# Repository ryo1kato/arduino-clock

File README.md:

## Arduino Blink "minute repeater" Clock (ATtiny85 version)

A clock with blinking LED indicating the time of day. &nbsp;
LED version of a [repeater](https://en.wikipedia.org/wiki/Repeater_%28horology%29)
You can tell a time in the dark, from distance, w/o glasses. &nbsp;
Useful if you're myopic and don't have glasses or smartphone within reach of your hand when you're in the bed (like me, with my two kids blocking my both sides). &nbsp;
LED brightness is automatically adjusted with light sensor (CdS photo cell)
The design uses AVR ATtiny85 micro controller and DS3231 RTC chip with "smart" RGB LED WS2812B.

## Telling Time
* Blinking in white: base hour of 0, 3, 6, or 9 o'clock.
    - once        : 0 o'clock
    - twice       : 3 o'clock
    - three times : 6 o'clock
    - four times  : 9 o'clock

* Blinking in <span style='color: #00AA00'>**green**</span>: add one or two hours to the above base hour.
    - example: blinking in white for three times, and then twice in green indicates 8 o'clock (8am or 8pm)

* Blinking in <span style='color: red'>**red**</span>: 10 minutes per blink.
    - example: blinking in red for four times: 40 minutes

* Blinking in <span style='color: blue'>**blue**</span>(fast): one minute per blink.

The clock blinks in white -> green -> blue -> blue, skipping some of the colors, for example, skipping red if the time is 10:02 (in which case it blinks in whilte three times, in green once, skips green, and in blue twice)

After completing this cycle, clock sleeps about 3 seconds and start a new cycle.

### Adjusting Time
Long press *Hour* and/or *Minute* button until they start blinking slowly in max brightness.

* Long press *Hour* button : advance time by 60 minutes (blinks in green)
* Long press *Minute* button : advance time by one minutes (blinks in blue)
* Long press **both** buttons : advance time by ten minutes (blinks in red)

You need to keep the buttons pressed and wait for an time indicating cycle to complete, until it starts blinking slowly and brightly.

### Build of Materials
* PCB
    - SMD (rev 0.5.1) [OSH Park](https://oshpark.com/shared_projects/CKZP3omf)
    - THT (rev 0.2) [OSH Park](https://oshpark.com/shared_projects/mC1U04Ox)
* BOM: [bom.txt](schematic/bom.txt)

### Port Assignment
* RST (GPIO #5) - Hour & Minute Buttons (using ADC above 2.2v reset threshold)
* GPIO #0       -  I2C SDA to RTC
* GPIO #1       -  Smart LED NeoPixel WS2812B
* GPIO #2       -  I2C SCL to RTC
* GPIO #3       -  Photo Cell
* GPIO #4       -  Power Control for LED, RTC, Photo Cell

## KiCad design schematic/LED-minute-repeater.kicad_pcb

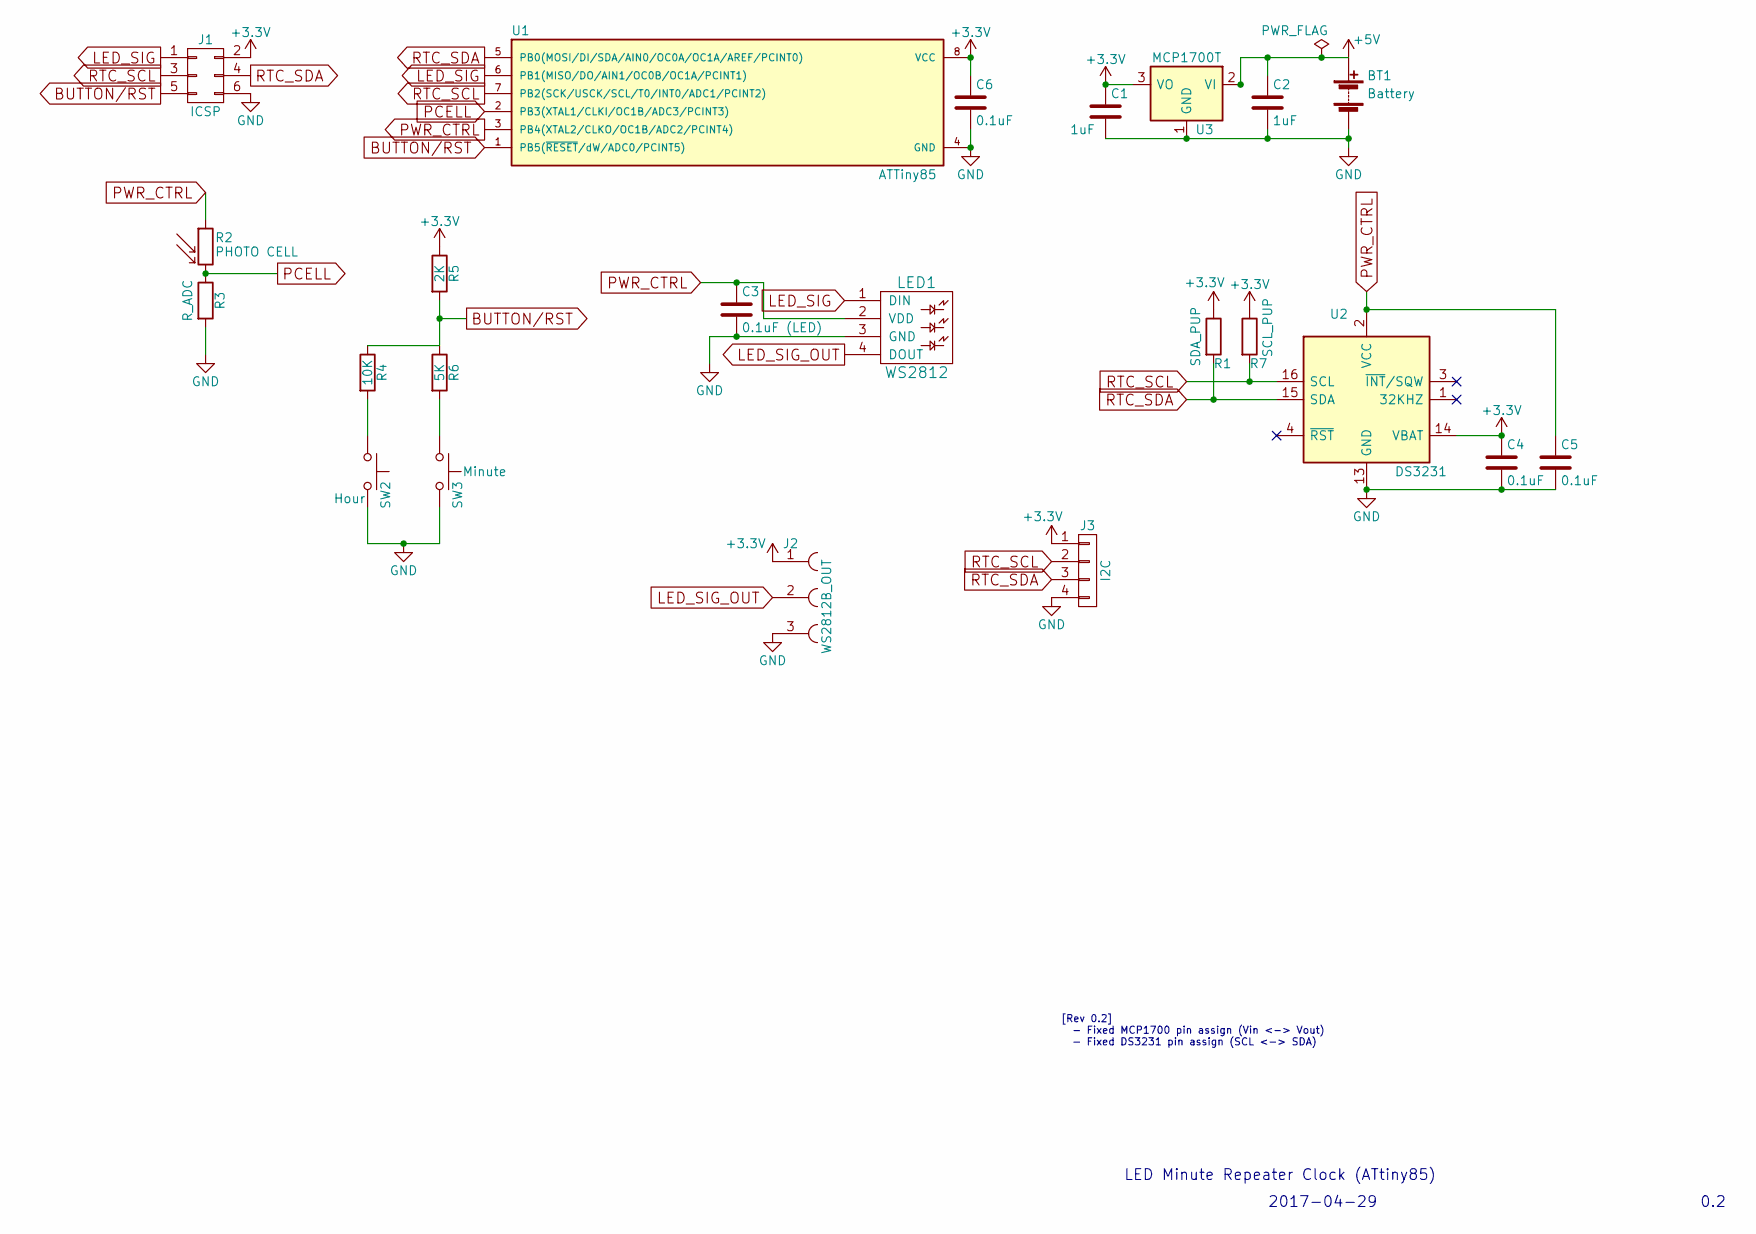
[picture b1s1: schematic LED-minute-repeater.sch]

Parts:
BT1: Battery; BatteryHolder_3xAAA_Keystone_2479
C1, C2: 1uF; C_0805_HandSoldering
C3: 0.1uF (LED); C_0805_HandSoldering
C4, C5, C6: 0.1uF; C_0805_HandSoldering
J1: ICSP; Pin_Header_Straight_2x03
J2: WS2812B_OUT; Pin_Header_Straight_1x03
J3: I2C; Pin_Header_Straight_1x04
LED1: WS2812; WS2812-8mm
R1: SDA_PUP; R_0805_HandSoldering
R2: PHOTO CELL; Resistor_LDR_4.9x4.2_RM2.54
R3: R_ADC; R_0805_HandSoldering
R4: 10K; R_0805_HandSoldering
R5: 2K; R_0805_HandSoldering
R6: 5K; R_0805_HandSoldering
R7: SCL_PUP; R_0805_HandSoldering
SW2: Hour; SW_SPST_EVQPE1
SW3: Minute; SW_SPST_EVQPE1
U1: ATTiny85; DIP-8_W7.62mm
U2: DS3231; SOIC-16W_7.5x10.3mm_Pitch1.27mm
U3: MCP1700T; SOT89-3_Housing_Handsoldering

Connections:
+3V3: C1.1, C4.1, C6.1, J1.2, J2.1, J3.1, R1.1, R5.1, R7.1, U1.8 (VCC), U2.14 (VBAT), U3.3 (VO)
+5V: BT1.1 (+), C2.1, U3.2 (VI)
BUTTON/RST: J1.5, R4.1, R5.2, R6.1, U1.1 (PB5(~RESET~/dW/ADC0/PCINT5))
GND: BT1.2 (-), C1.2, C2.2, C3.2, C4.2, C5.2, C6.2, J1.6, J2.3, J3.4, LED1.3 (GND), R3.2, SW2.2, SW3.2, U1.4 (GND), U2.5 (NC), U2.6 (NC), U2.7 (NC), U2.8 (NC), U2.9 (NC), U2.10 (NC), U2.11 (NC), U2.12 (NC), U2.13 (GND), U3.1 (GND)
LED_SIG: J1.1, LED1.1 (DIN), U1.6 (PB1(MISO/DO/AIN1/OC0B/OC1A/PCINT1))
LED_SIG_OUT: J2.2, LED1.4 (DOUT)
unnamed: R4.2, SW2.1
unnamed: R6.2, SW3.1
PCELL: R2.2, R3.1, U1.2 (PB3(XTAL1/CLKI/OC1B/ADC3/PCINT3))
PWR_CTRL: C3.1, C5.1, LED1.2 (VDD), R2.1, U1.3 (PB4(XTAL2/CLKO/OC1B/ADC2/PCINT4)), U2.2 (VCC)
RTC_SCL: J1.3, J3.2, R7.2, U1.7 (PB2(SCK/USCK/SCL/T0/INT0/ADC1/PCINT2)), U2.16 (SCL)
RTC_SDA: J1.4, J3.3, R1.2, U1.5 (PB0(MOSI/DI/SDA/AIN0/OC0A/OC1A/AREF/PCI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), U2.15 (SDA)

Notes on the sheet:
2017-04-29
LED Minute Repeater Clock (ATtiny85)
0.2
[Rev 0.2] - Fixed MCP1700 pin assign (Vin <-> Vout) - Fixed DS3231 pin assign (SCL <-> SDA)

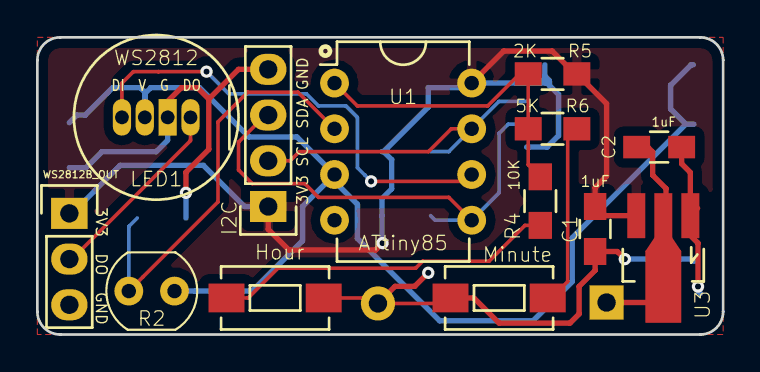
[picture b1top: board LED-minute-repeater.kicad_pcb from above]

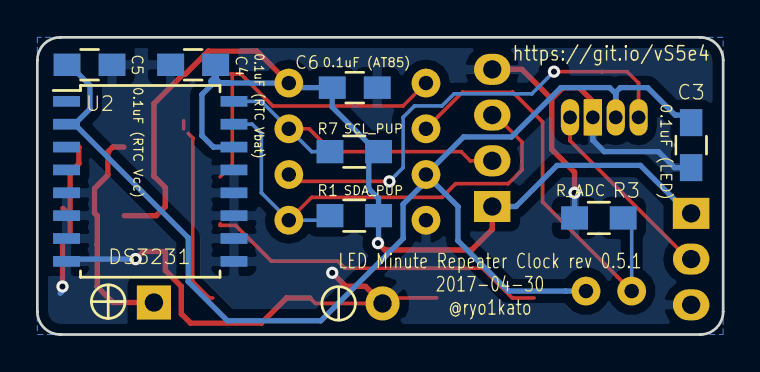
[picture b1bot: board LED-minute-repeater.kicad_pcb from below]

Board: 2 copper layers, 38.1 x 16.5 mm, 22 parts (9 on the bottom side), 12 nets.

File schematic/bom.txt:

BOM for SMD version (rev 0.5.1) of the board: https://oshpark.com/shared_projects/CKZP3omf
There's an THT version of the board too. https://oshpark.com/shared_projects/mC1U04Ox - Simply chagne C and R to THT versions.

Digi-Key Cart: http://www.digikey.com/short/3nb1p4 (Except WS2812B LED)

SW3   Minute       Panasonic Electronic Components EVQ-PE104K
U1    ATTiny85     ATTINY85-20PU-ND (DIP8)
R2    PHOTO CELL   Photo resister 10~100k ohm @ 10lux
R3    R_ADC        0805(2012 metric) 4.7K ohm, or adjust resistance based on photo cell resistance characteristic
SW2   Hour         Panasonic Electronic Components EVQ-PE104K
R4    10K          0805(2012 metric)
U2    DS3231       DS3231SN (SOIC-16W)
BT1   Battery      Keystone 36-2479-ND
R6    5K           0805(2012 metric) 5K ohm (4.7K ohm works as well)
R5    2K           0805(2012 metric) 2K ohm
J2    WS2812B_OUT  Pin_Headers:Pin_Header_Straight_1x03
J1    ICSP         Pin_Headers:Pin_Header_Straight_2x03
U3    MCP1700T     MCP1700T-3302E/MB (SOT89)
C2    1uF          0805(2012 metric)
C1    1uF          0805(2012 metric)
J3    I2C          Pin_Headers:Pin_Header_Straight_1x04
R7    SCL_PUP      0805(2012 metric) 4.7K ohm
R1    SDA_PUP      0805(2012 metric) 4.7K ohm
LED1  WS2812       WS2812-8mm: Designed for  https://www.adafruit.com/product/1734, but only tested with https://www.amazon.com/dp/B01D1FFVOA
C4    0.1uF        0805(2012 metric)
C5    0.1uF        0805(2012 metric)
C6    0.1uF        0805(2012 metric)
C3    0.1uF (LED)  0805(2012 metric) for WS2812B. You don’t need this when using https://www.amazon.com/dp/B01D1FFVOA

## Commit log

2017-03-05 first working version with LED blink + eeprom
2017-03-05 auto brightness adj with photocell
2017-03-05 adj port assignment, remove debug msg
2017-03-06 adjust brightness
2017-03-06 add schematics
2017-03-06 add README
2017-03-16 Support for Adafruit Trinket
2017-03-18 first NeoPixel-on-Trinket version
2017-03-19 fix compile error for Uno/nano
2017-03-21 use photocell for nano boards
2017-03-25 Using DS3231 RTC module
2017-03-29 Use TinyRTCLib and Narcoleptic
2017-04-01 ADC power save
2017-04-01 diable RTC 32Khz, fix compiler warning
2017-04-09 replace delay() with msleep() for clarity
2017-04-15 remove reference counting, etc.
2017-04-15 update schematic
2017-04-15 adding README.md
2017-04-15 fix I2C header silk position
2017-04-15 schematic: fix DS3231 silk
2017-04-29 fix reg and RTC chip pin assign swap
2017-04-29 PCB layout for rev 0.2 circuit
2017-05-01 Smaller size SMD version of PCB
    OSH Order #MdFUZar9
    Erratta:
    - I2C GND is not connected
    - Reg (MCP1700) GND is not connected
2017-05-06 rev 0.5.1 - errata fix for rev0.5
2017-05-08 add bom.txt and update README
2017-05-08 Save time to EEPROM
2017-11-25 add narcoleptic as submodule
